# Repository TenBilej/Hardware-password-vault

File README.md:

### HARDWARE

Hardware in this project is licensed under modified **CERN Open Hardware Licence Version 2 – Strongly Reciprocal (CERN-OHL-S) with NonCommercial restriction**.

- You may **use, modify, and share** the hardware design for **non-commercial purposes only**.
- **Original author(s) must be credited** in any copy or derivative work.
- **Patent rights** are granted according to the CERN-OHL-S terms.
- For **commercial use**, you must obtain a separate license from the author.
- For **commercial use**, please contact the author: **TenBilej@protonmail.com**.

### SOFTWARE

The software included in this project is licensed under the **MIT License**.

- You may use, copy, modify, merge, publish, distribute, sublicense, and/or sell copies of the software.
- **Original author(s) must be credited**.

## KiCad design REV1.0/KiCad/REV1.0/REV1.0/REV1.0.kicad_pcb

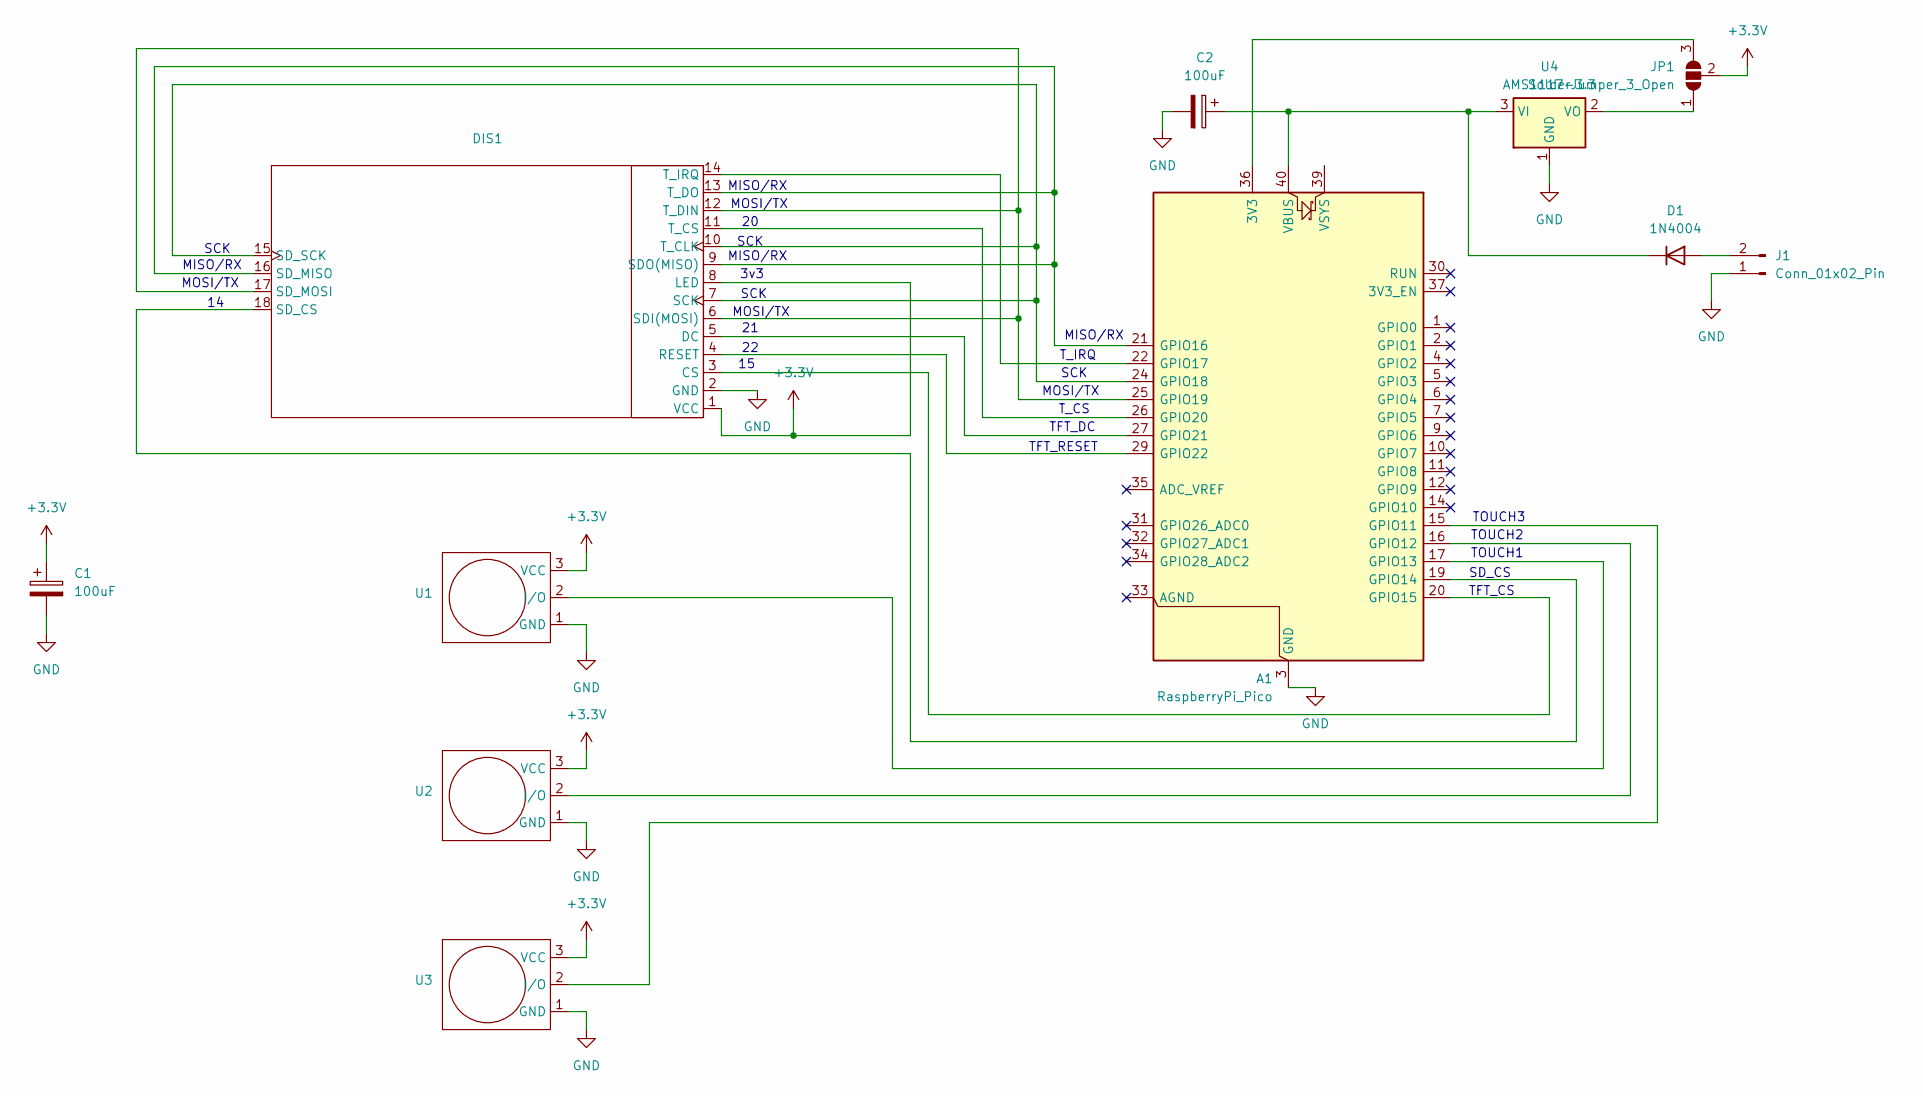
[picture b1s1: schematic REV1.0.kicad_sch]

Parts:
A1: RaspberryPi_Pico; RaspberryPi_Pico_SMD
C1, C2: 100uF; CP_Axial_L18.0mm_D6.5mm_P25.00mm_Horizontal
D1: 1N4004; D_DO-41_SOD81_P10.16mm_Horizontal
DIS1: 2,4 TFT SPI 240x320
J1: Conn_01x02_Pin; con biely
JP1: SolderJumper_3_Open; SolderJumper-3_P2.0mm_Open_TrianglePad1.0x1.5mm_NumberLabels
U1, U2, U3: touch
U4: AMS1117-3.3; SOT-223-3_TabPin2

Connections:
+3.3V: C1.1, DIS1.1 (VCC), DIS1.8 (LED), JP1.2 (C), U1.3 (VCC), U2.3 (VCC), U3.3 (VCC)
GND: A1.3 (GND), A1.8 (GND), A1.13 (GND), A1.18 (GND), A1.23 (GND), A1.28 (GND), A1.38 (GND), C1.2, C2.2, DIS1.2 (GND), J1.1, U1.1 (GND), U2.1 (GND), U3.1 (GND), U4.1 (GND)
unnamed: A1.36 (3V3), JP1.3 (B)
unnamed: A1.15 (GPIO11), U3.2 (I/O)
unnamed: A1.16 (GPIO12), U2.2 (I/O)
unnamed: A1.17 (GPIO13), U1.2 (I/O)
unnamed: A1.19 (GPIO14), DIS1.18 (SD_CS)
unnamed: A1.20 (GPIO15), DIS1.3 (CS)
unnamed: A1.21 (GPIO16), DIS1.9 (SDO(MISO)), DIS1.13 (T_DO), DIS1.16 (SD_MISO)
unnamed: A1.22 (GPIO17), DIS1.14 (T_IRQ)
unnamed: A1.24 (GPIO18), DIS1.7 (SCK), DIS1.10 (T_CLK), DIS1.15 (SD_SCK)
unnamed: A1.25 (GPIO19), DIS1.6 (SDI(MOSI)), DIS1.12 (T_DIN), DIS1.17 (SD_MOSI)
unnamed: A1.26 (GPIO20), DIS1.11 (T_CS)
unnamed: A1.27 (GPIO21), DIS1.5 (DC)
unnamed: A1.29 (GPIO22), DIS1.4 (RESET)
unnamed: A1.40 (VBUS), C2.1, D1.1 (K), U4.3 (VI)
unnamed: D1.2 (A), J1.2
unnamed: JP1.1 (A), U4.2 (VO)

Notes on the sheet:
SCK
TFT_RESET
T_CS
MISO/RX
T_IRQ
TOUCH3
MOSI/TX
3v3
TOUCH2
TFT_DC
TOUCH1
TFT_CS
SD_CS

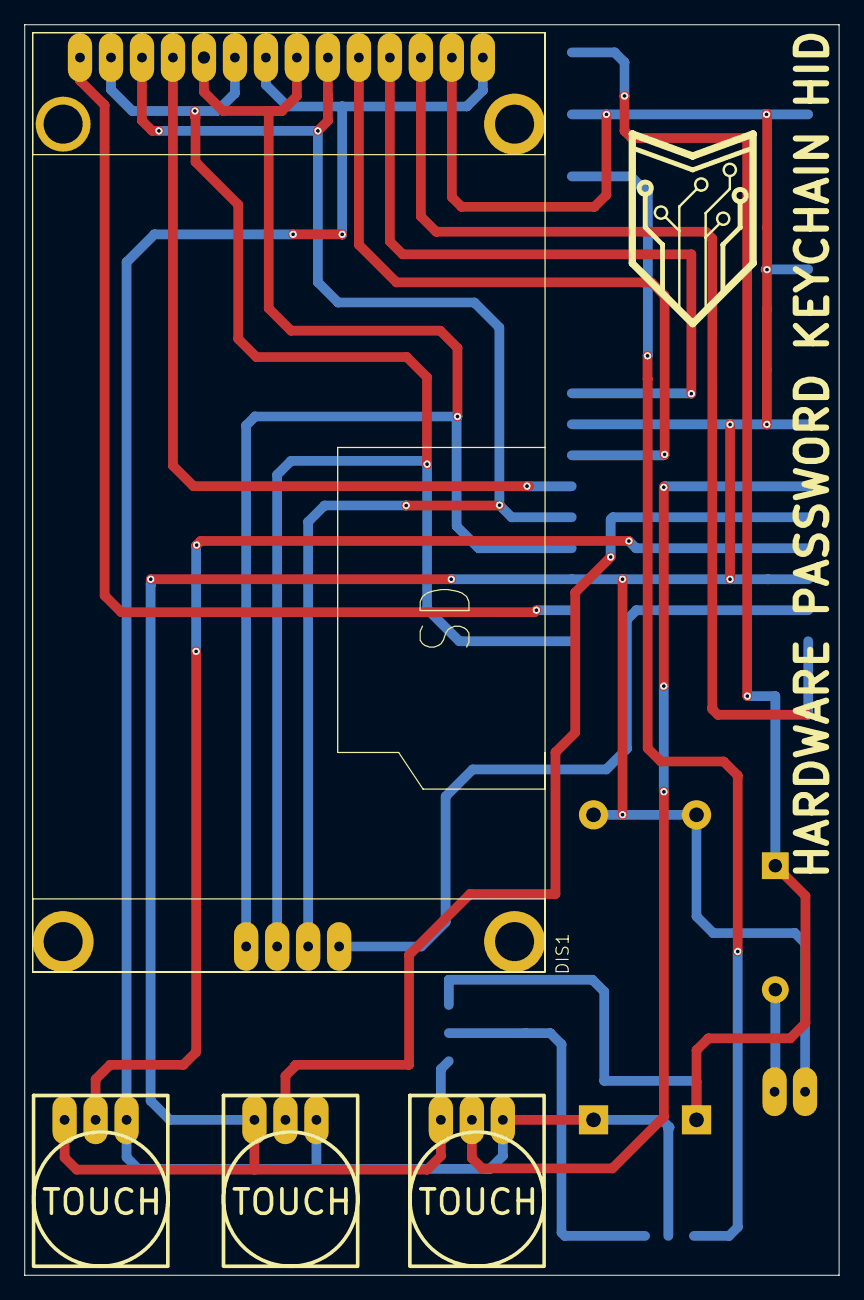
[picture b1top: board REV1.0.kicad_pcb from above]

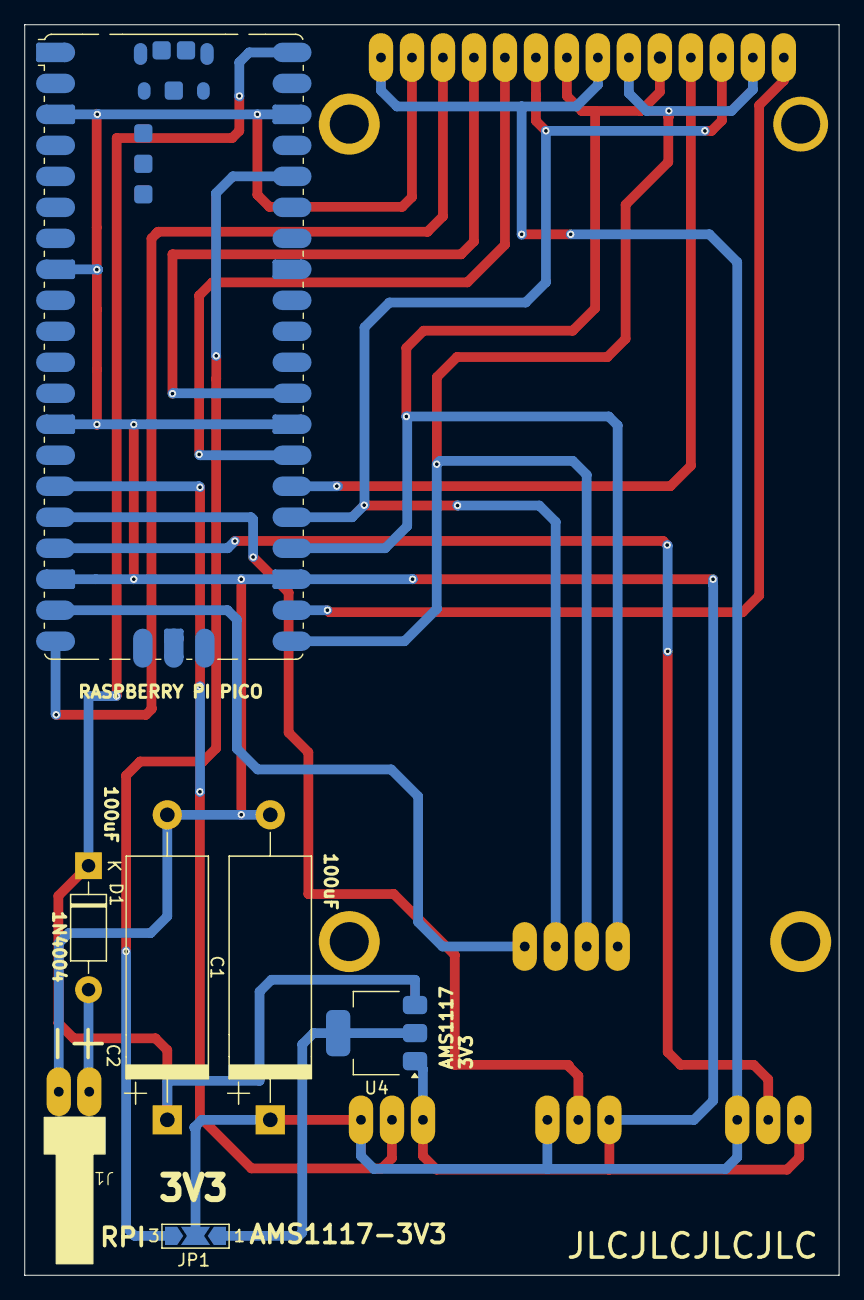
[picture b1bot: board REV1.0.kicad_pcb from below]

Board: 2 copper layers, 66.8 x 102.5 mm, 11 parts (7 on the bottom side), 18 nets.

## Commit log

2025-10-15 Update LICENSE
2025-10-15 Rename LICENSE to HARDWARE LICENSE
2025-10-15 Create SOFTWARE LICENCE
